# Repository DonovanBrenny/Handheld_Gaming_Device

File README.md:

# Handheld Gaming Device

A PIC24FJ64GA002 handheld game console with a 128x128 OLED, dual analog
joysticks, and four built-in games. Firmware in C, hardware in KiCad.

## Games

- **Pong** - two-player, first to 5
- **Ackanoid** - brick breaker, 3 levels, 3 lives
- **Maze** - 2.5D raycaster on a randomly generated maze
- **Dinosaur Runner** - endless side-scroller, jump with the blue button

## Controls

- **Joysticks** - menu navigation and in-game movement
- **Blue button** - select / jump
- **Red button** - back
- **Joystick click + Red (held)** - exit a game to the main menu

## Build

MPLAB X IDE + XC16 compiler. Open the `.X` folder as a project, build, and
flash with a PICkit (or equivalent) via the ICSP header.

## Hardware

KiCad schematic and PCB live in `hardware/`. Built around a PIC24FJ64GA002
(28-pin DIP), an SH1107-class 128x128 OLED on SPI1, two analog joysticks,
two pushbuttons, and an NPN-driven piezo speaker. Pin assignments are in
[`Setup.c`](Setup.c).

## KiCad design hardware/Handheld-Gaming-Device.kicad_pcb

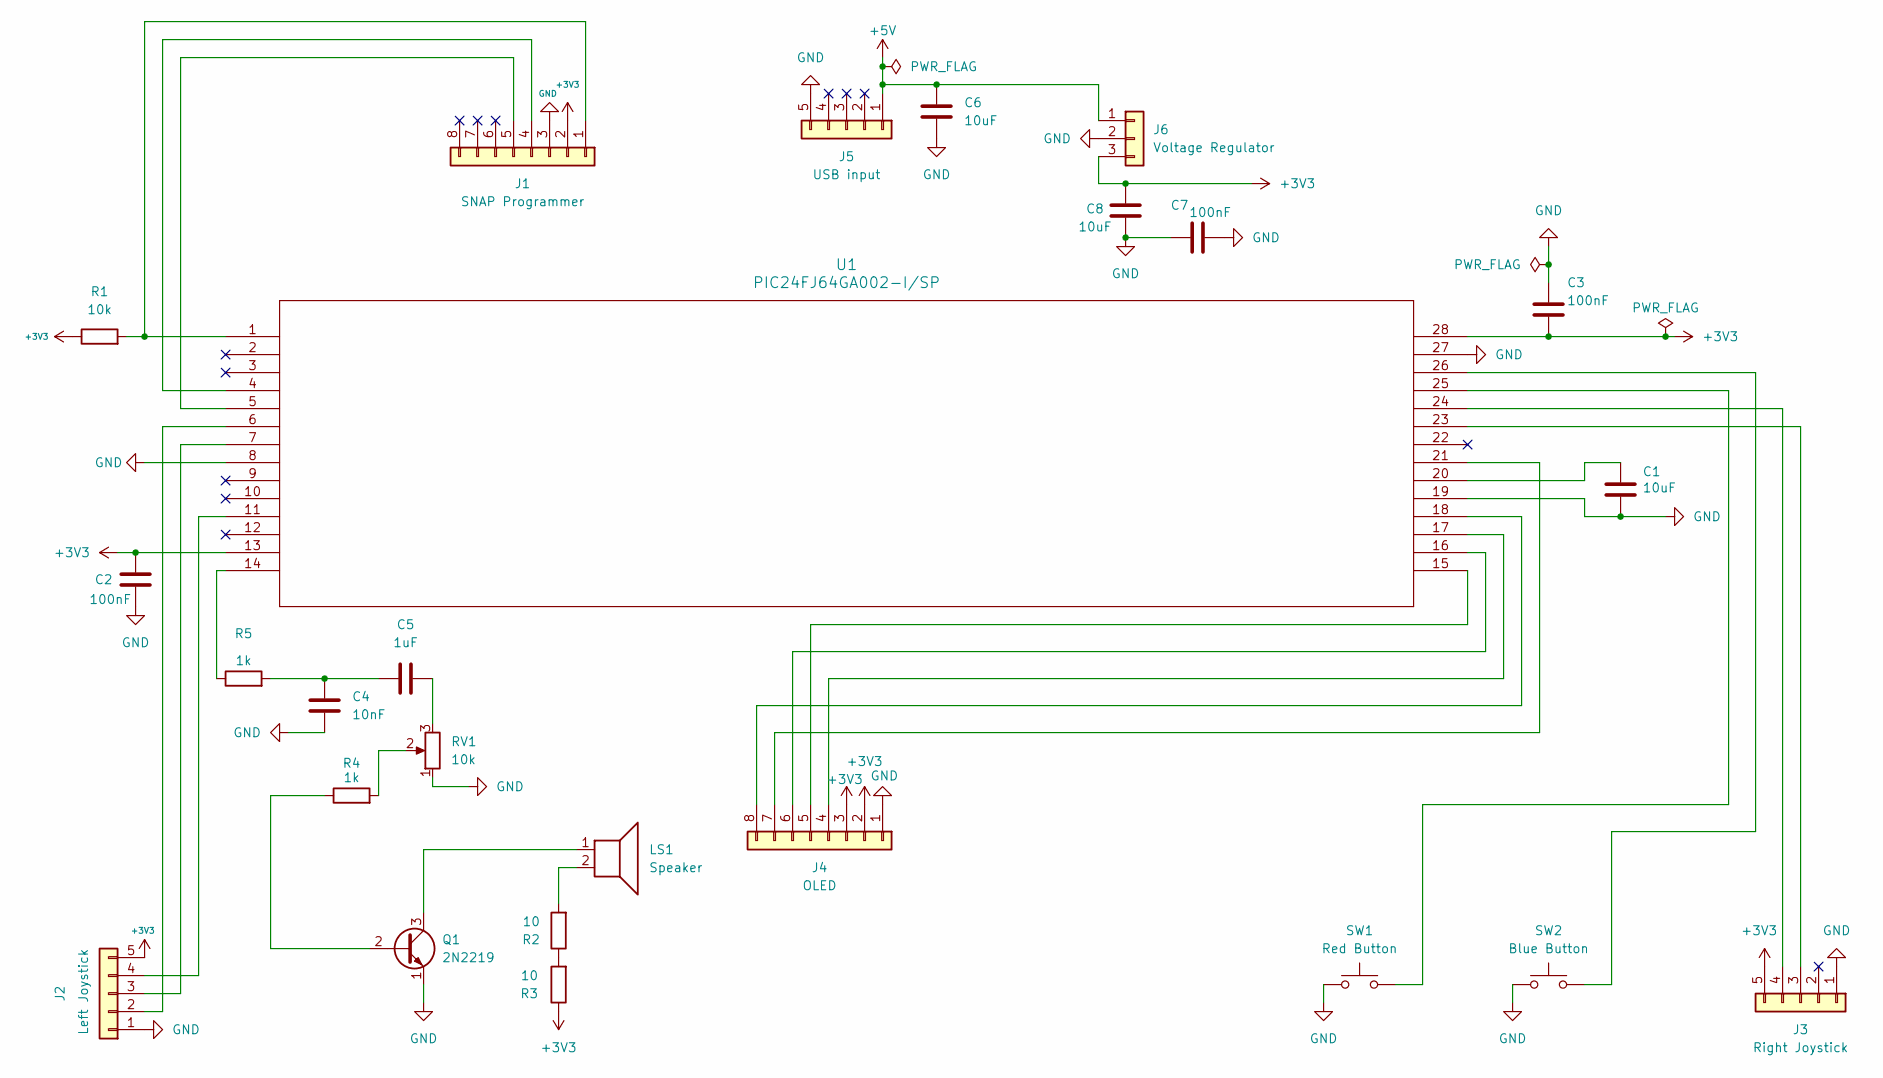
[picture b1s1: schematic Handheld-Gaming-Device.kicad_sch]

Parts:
C1, C6, C8: 10uF; C_Disc_D5.0mm_W2.5mm_P5.00mm
C2, C3, C7: 100nF; C_Disc_D5.0mm_W2.5mm_P5.00mm
C4: 10nF; C_Disc_D5.0mm_W2.5mm_P5.00mm
C5: 1uF; C_Disc_D5.0mm_W2.5mm_P5.00mm
J1: SNAP Programmer; PinSocket_1x08_P2.54mm_Vertical
J2: Left Joystick; PinSocket_1x05_P2.54mm_Vertical
J3: Right Joystick; PinSocket_1x05_P2.54mm_Vertical
J4: OLED; PinSocket_1x08_P2.54mm_Vertical
J5: USB input; PinSocket_1x05_P2.54mm_Vertical
J6: Voltage Regulator; TO-220-3_Vertical
LS1: Speaker; PinHeader_1x02_P2.54mm_Vertical
Q1: 2N2219; TO-39-3
R1: 10k; R_Axial_DIN0207_L6.3mm_D2.5mm_P10.16mm_Horizontal
R2, R3: 10; R_Axial_DIN0207_L6.3mm_D2.5mm_P10.16mm_Horizontal
R4, R5: 1k; R_Axial_DIN0207_L6.3mm_D2.5mm_P10.16mm_Horizontal
RV1: 10k; Potentiometer_Bourns_3386P_Vertical
SW1: Red Button; SW_PUSH_6mm
SW2: Blue Button; SW_PUSH_6mm
U1: PIC24FJ64GA002-I/SP; DIP-28_W7.62mm

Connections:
+3V3: C2.1, C3.2, C8.1, J1.2, J2.5, J3.5, J4.2, J4.3, J6.3, R1.1, R3.1, U1.13, U1.28
+5V: C6.1, J5.1, J6.1
GND: C1.2, C2.2, C3.1, C4.1, C6.2, C7.1, C7.2, C8.2, J1.3, J2.1, J3.1, J4.1, J5.5, J6.2, Q1.1 (E), RV1.1, SW1.1, SW2.1, U1.8, U1.19, U1.27
unnamed: C1.1, U1.20
unnamed: C4.2, C5.1, R5.2
unnamed: C5.2, RV1.3
unnamed: J1.1, R1.2, U1.1
unnamed: J1.4, U1.4
unnamed: J1.5, U1.5
unnamed: J2.2, U1.6
unnamed: J2.3, U1.7
unnamed: J2.4, U1.11
unnamed: J3.3, U1.23
unnamed: J3.4, U1.24
unnamed: J4.4, U1.17
unnamed: J4.5, U1.15
unnamed: J4.6, U1.16
unnamed: J4.7, U1.21
unnamed: J4.8, U1.18
unnamed: LS1.2, R2.2
unnamed: Q1.2 (B), R4.1
unnamed: LS1.1, Q1.3 (C)
unnamed: R2.1, R3.2
unnamed: R4.2, RV1.2
unnamed: R5.1, U1.14
unnamed: SW1.2, U1.25
unnamed: SW2.2, U1.26

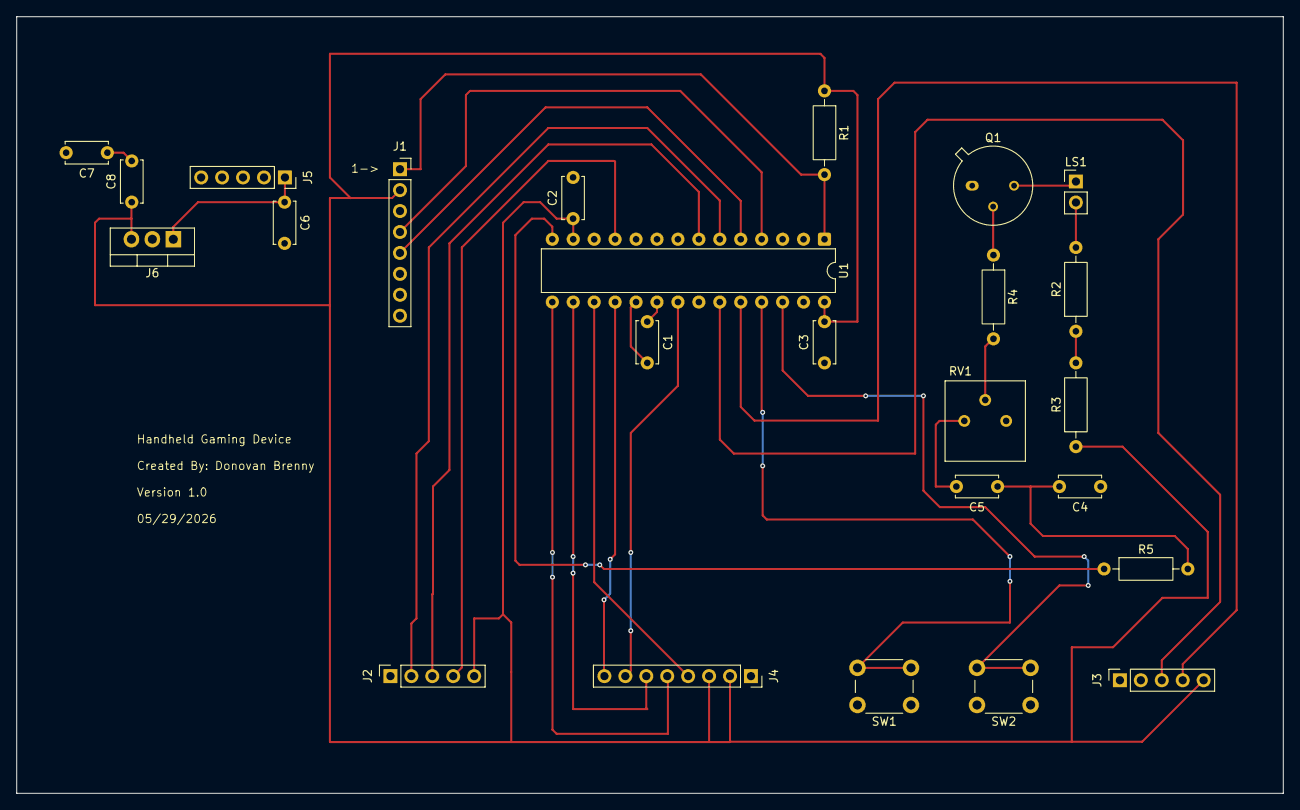
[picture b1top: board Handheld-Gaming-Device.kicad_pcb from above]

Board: 2 copper layers, 153.7 x 94.2 mm, 25 parts (0 on the bottom side), 27 nets.

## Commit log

2026-05-29 Add README for handheld gaming device project
    Added detailed information about the handheld gaming device, including games, controls, build instructions, and hardware specifications.
2026-05-29 Uploaded all device files
    The whole handheld gaming device files
2026-05-29 PCB design change
    Changed the layout and size of the PCB
